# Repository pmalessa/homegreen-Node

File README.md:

# HomeGreen - self watering system
## Description
A self watering system for outdoor plants. This project contains the hardware and software files to completely build a HomeGreen node on your own.

The system is based on an inexpensive node, which is able to control up to 3 pumps and can be powered by nearly any conventional powerbank. It has a basic user interface using a 6-Digit 7-Segment Display combined with 4 touch buttons. As a pump, you could either use a 4-6V DC pump or a 5V relay to control a higher voltage pump. The node is designed to be water resistant and can be easily mounted using embedded magnets or a 3D printed holder.

## Repository structure
This repo contains everything you need to build a homegreen node on your own:

- hardware: The EAGLE PCB and GERBER files, BOM and models and dimensions for the case
- firmware: The firmware for the microcontroller (attiny88) on the node

## Hardware
The HomeGreen node PCB is designed to be enclosed in a 25mm diameter transparent pipe to be water resistant. The touch buttons can be used through the pipe without the need to open the case. The 2 ends need plastic caps, which could be easily 3D printed. one needs to be fully closed, while the other one needs to have an opening the for USB-A connector of the pump as well as the micro USB connector of the powerbank.

## Firmware
The firmware is written in low-level C++ and uses the PlatformIO framework. It is designed to run as energy efficient as possible to be able to run on a powerbank for a long time.

## Detailed description
The HomeGreen node contains the following main components:
- an attiny88 microcontroller as main controller
- a sophisticated power management circuit to be able to sleep and wake up the connected powerbank regularly
- a 6-Digit 7-Segment Display with its controller as user interface
- a 4-Channel touch button controller as user interface
- an I2C temperature sensor to measure the temperature of the environment
- a current limiter, step-up converter and a current measurement circuit to adjust and monitor the output power for the pump
- the ability to control up to 3 pumps sequentially using an additional HomeGreen Pump Hub

### Power management
The main issue of supplying your gadgets using a powerbank is the fact, that nearly all powerbanks shut off after a certain time of inactivity. As the sleep current draw of the HomeGreen node is substantially lower than any charge current the powerbank is designed for, it treats it as inactive and shuts off eventually. 

This led to the necessity to have a supercapacitor as an additional short-time energy storage onboard to be able to power the controller while in sleep and only wake the powerbank once the supercap is drained or it is time to enable the pump.

Additionally, each powerbank is behaving differently when it comes to the sleep and wake behavior. Some powerbanks wake up immediately once you connect the capacitive load of the supercap, while others require an additional substantial resistive load to enable its regulators. Strangely, some powerbanks even change their polarity and apply -2.5V to their output!

To support most of the available powerbanks on the market 2 MOSFETS back to back, combined with a charge pump and an additional controllable resistive load was necessary. Even with that, some powerbanks do not work reliably and should be avoided. A list of tested powerbanks will be added.

### User Interface
The HomeGreen Node consists of a 6-Digit 7-Segment display as well as 4 touch buttons to view its status and adjust all parameters to your needs. The HomeGreen Node can be used to control up to 3 pumps using an additional HomeGreen Pump Hub. Once connected, the user interface switches to the ability to adjust timing of each pump separately. However, if no Pump Hub is connected, it is simplyfied to control just one pump.

#### Sleep State
In its default sleep state, the 7-Segment Display is turned off and only the 2 Status LEDs are displaying its state. 
- If it blinks green once every 8 seconds, everything is fine. 
- If it blinks green twice and in a faster interval, it charges its supercap. This happens every 5-15mins. 
- If it blinks red, an error occured and the Node should be checked by waking it to get more details.
- If it is time to water the plants, it will wake itself and continue with the Pump State.
- To wake the Node, just touch one of its touch buttons. It will then try to wake the powerbank and will turn on its Display, once successful. It may take multiple tries sometimes depending on the model of powerbank. It then moves into Info State. If an error occured, it will switch into Error State after wake up before going to Info State.

#### Info State
In the info state, you see the set interval and duration of the pump cycle as well as the time left till the next pump cycle at one glance. If a Pump Hub is connected, you can switch between the config for each pump with a short press of the SET button.
- If no button is pressed, it shuts off and switches back to Sleep State after some time.
- To adjust the interval or duration of the pump cycle, long press the SET button and wait for the display to fade out and in. It now switched into Config State.
- To start a manual pump cycle, just long press the MANUAL button. It then switches into Pump State.

#### Config State
In the Config State, you can adjust the interval and duration of the pump cycle. The currently selected parameter is displayed by blinking its number.
- To increase the parameter, short press or hold the + button.
- To decrease the parameter, short press of hold the - button.
- To switch the selected parameter, short press the SET button.
- To save the newly configured parameters, long press the SET button. It switches to Info State then.
- If no button have been pressed for a longer period, changes are discarded and it switches to Info State.
- To get more advanced information and configuration options, long press the MANUAL button to switch to Advanced State.

#### Pump State
Once the pump interval elapsed or a manual pump cycle has been started, the Node switches into Pump State. In Pump State, an animation is displayed as well as the time left to pump in the current cycle. If a Pump Hub is connected, it will additionally display which pump is currently enabled.
- To increase the current pump cycle by 1 minute, short press the + button.
- To decrease the current pump cycle by 1 minute, short press the - button.
- To manually switch to the next pump, short press the SET button.
- To stop the current pump cycle, long press the MANUAL button.
- Once the pump duration of all pumps elapsed, the Node will switch to Info State to shortly display its current parameters, and after some time of inactivity it switches back to Sleep State.

#### Error State
If an error ocurred, the red led blinks to signal that something went wrong. To check for details, wake the node and it will switch to this state.
The following errors are possible:
- PB_ERR: Powerbank-Error - The node was not possible to wake the powerbank at its last wake up by a pump cycle or a user action. Check the charge state or cabling of the powerbank. Maybe that model is incompatible with the Node, check the list of tested powerbanks for hints.
- P1_ERR/P2_ERR/P3_ERR: Pump1/2/3-Error - There is an issue with the mentioned pump, the current draw had an anomaly. Maybe the cable is broken, the water tank is empty or the pump is clogged.
- EP_ERR: EEPROM-Error - There is an issue with the save state of the configuration. This rarely happens, but sometimes the config can get corrupted by battery drain. The config will be reset to default state and it has to be reconfigured.

The following interactions are possible:
- To clear the current error, short press any button.
- To ignore the current error permanently (until the next reset to defaults), long press the MANUAL button.

#### Advanced State
The Advanced State contains additional information and configuration options to move through.
The following informations are displayed:
- The build date of the firmware
- The build version of the firmware
- The current runtime in hours
- The total runtime in hours

The following interactions are possible:
- To move to the next information, short press the SET button
- To leave the Advanced State back to Info State, long press the SET button
- To reset all configurations to its default state, long press the MANUAL button. It then switches back to Info State.

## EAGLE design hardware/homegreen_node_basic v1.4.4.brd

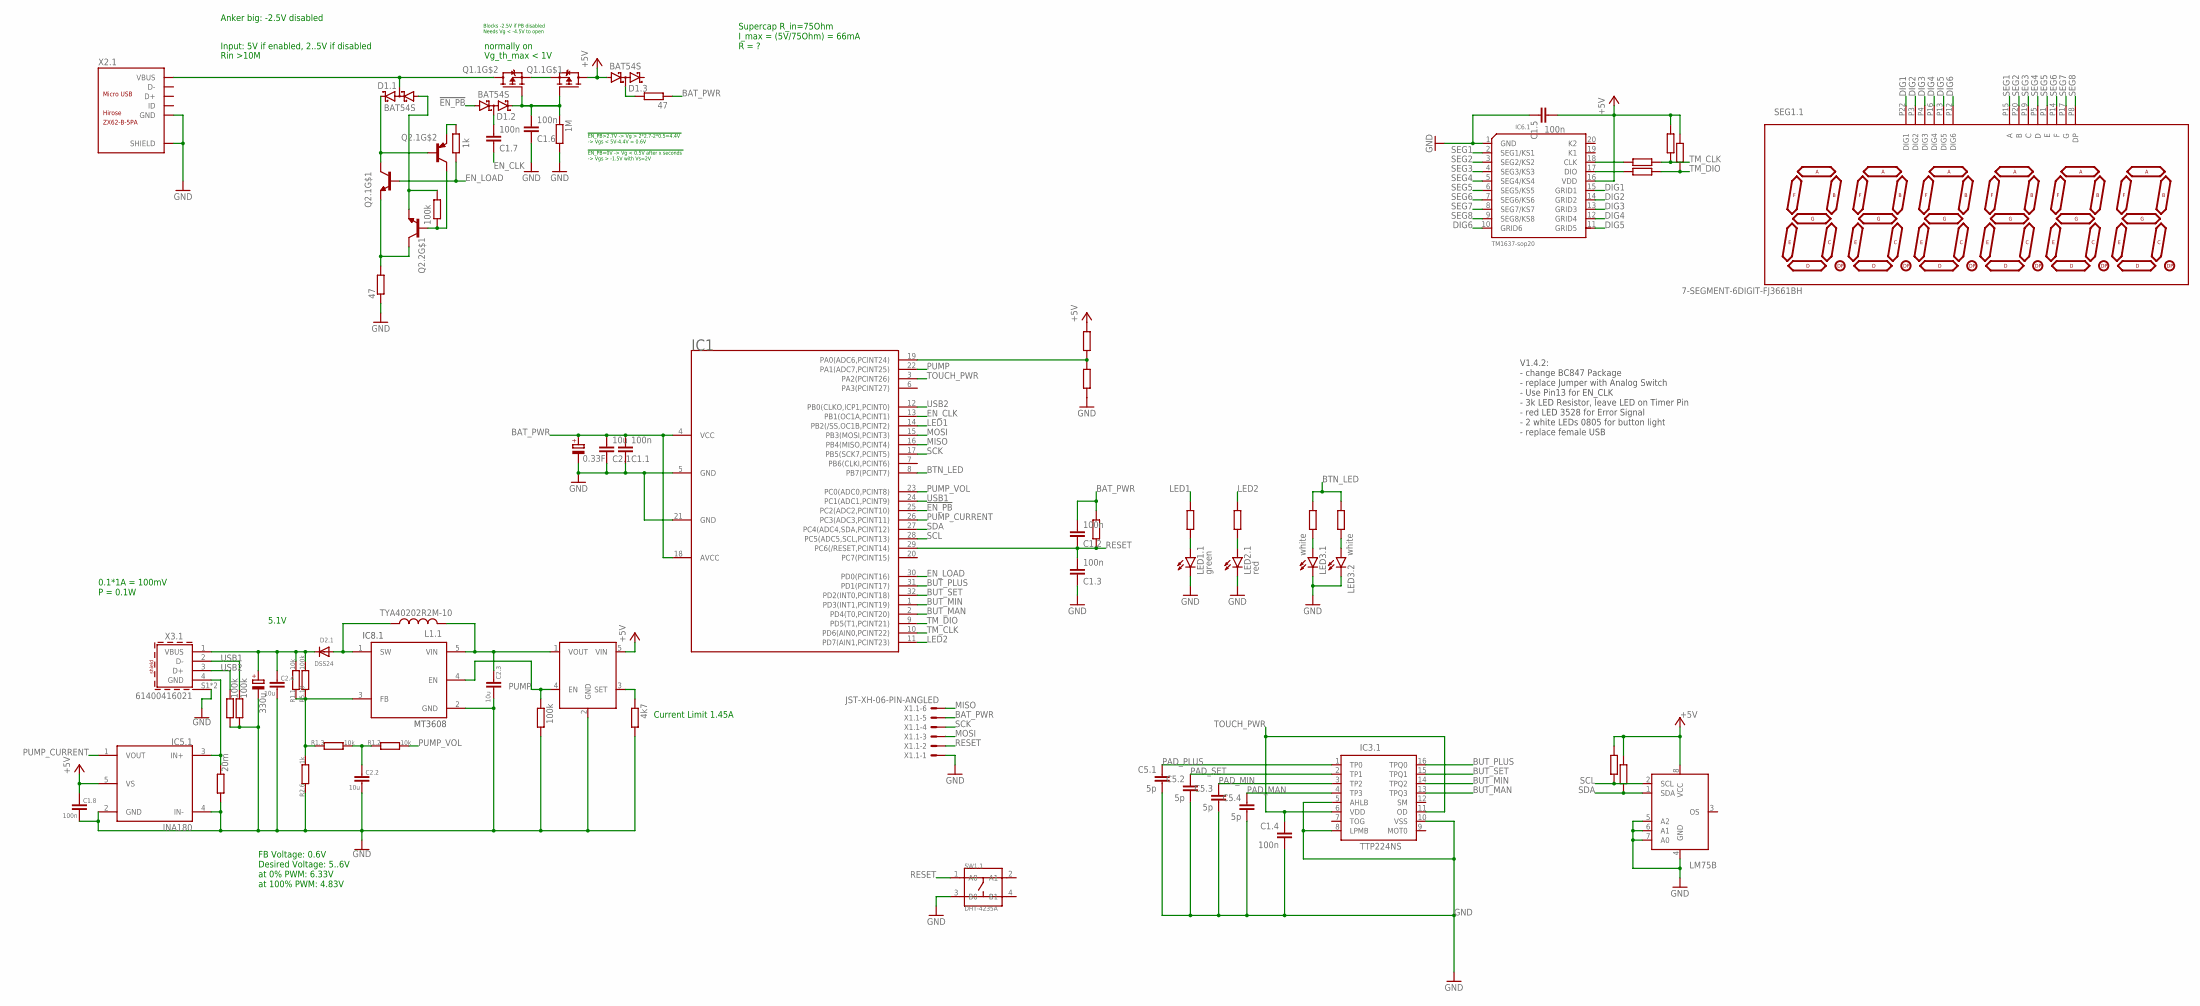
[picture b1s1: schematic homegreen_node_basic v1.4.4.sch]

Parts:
C1.1, C1.2, C1.3, C1.4, C1.5, C1.6, C1.7, C1.8: 100n; C0805
C2.1, C2.2, C2.3, C2.4: 10u; C0805
C3.1: 0.33F; C_FYD0H104ZF
C4.1: 330u; PANASONIC_D
C5.1, C5.2, C5.3, C5.4: 5p; C0805
D1.1, D1.2, D1.3: BAT54S; SOT23
D2.1: DSS24; SOD-123
IC1: ATTINY88; TQFP32-08
IC2.1: LM75B; SO8
IC3.1: TTP224NS; SSOP16
IC4.1: MT9700MT9700; SOT23-5
IC5.1: INA180; SOT23-5
IC6.1: TM1637-sop20; SOP20-1.27-12.7X7.65MM
IC8.1: MT3608; SOT23-6
L1.1: TYA40202R2M-10; WE-LQSH_4020
LED1.1: green; KA-3528ASYC
LED2.1: red; KA-3528ASYC
LED3.1, LED3.2: white; CHIPLED_0805
Q1.1: WST2011; SOT23-6
Q2.1, Q2.2: BC817DPN; SOT23-6
R1.1, R1.2, R1.3: 10k; R0805
R2.1, R2.2, R2.3, R2.4, R2.5, R2.6: 1k; R0805
R3.1, R3.2: 47; R0805
R4.1, R4.2: 3k; R0805
R5.1, R5.2, R5.3, R5.4, R5.5, R5.6, R5.7, R5.8, R5.9, R5.10: 100k; R0805
R6.1: 1M; R0805
R7.1, R7.2, R7.3: 4k7; R0805
R8.1: 20m; R0805
SEG1.1: 7-SEGMENT-6DIGIT-FJ3661BH; 7SEG_6D_FJ3661BH
SW1.1: DHT-4235A; SW4-SMD-4.2X3.2X2.5MM
X1.1: JST-XH-06-PIN-ANGLED; JST-XH-06-PACKAGE-ROUND-PAD-ANGLED
X2.1: ZX62-B-5PA
X3.1: 61400416021

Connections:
!EN_PB: D1.2.1 (A1), IC1.25 (PC2(ADC2,PCINT10))
+5V: C1.5.2, C1.8.1, D1.3.1 (A1), IC2.1.8 (VCC), IC4.1.5 (VIN), IC5.1.5 (VS), IC6.1.16 (VDD), Q1.1.6 (D), R5.3.1, R5.5.2, R5.6.2, R7.2.2, R7.3.2
BAT_PWR: C1.1.2, C1.2.2, C2.1.2, C3.1.+, IC1.4 (VCC), IC1.18 (AVCC), R3.2.1, R5.7.1, X1.1.5
BTN_LED: IC1.8 (PB7(PCINT7)), R2.1.2, R2.5.2
BUT_MAN: IC1.2 (PD4(T0,PCINT20)), IC3.1.13 (TPQ3)
BUT_MIN: IC1.1 (PD3(INT1,PCINT19)), IC3.1.14 (TPQ2)
BUT_PLUS: IC1.31 (PD1(PCINT17)), IC3.1.16 (TPQ0)
BUT_SET: IC1.32 (PD2(INT0,PCINT18)), IC3.1.15 (TPQ1)
DIG1: IC6.1.15 (GRID1), SEG1.1.P22 (DIG1)
DIG2: IC6.1.14 (GRID2), SEG1.1.P3 (DIG2)
DIG3: IC6.1.13 (GRID3), SEG1.1.P4 (DIG3)
DIG4: IC6.1.12 (GRID4), SEG1.1.P16 (DIG4)
DIG5: IC6.1.11 (GRID5), SEG1.1.P13 (DIG5)
DIG6: IC6.1.10 (GRID6), SEG1.1.P12 (DIG6)
EN_CLK: C1.7.1, IC1.13 (PB1(OC1A,PCINT1))
EN_LOAD: IC1.30 (PD0(PCINT16)), Q2.1.2 (B), R2.4.1
GND: C1.1.1, C1.3.1, C1.4.2, C1.5.1, C1.6.1, C1.8.2, C2.1.1, C2.2.2, C2.3.2, C2.4.2, C3.1.-, C4.1.-, C5.1.2, C5.2.2, C5.3.2, C5.4.2, IC1.5 (GND), IC1.21 (GND), IC2.1.4 (GND), IC2.1.5 (A2), IC2.1.6 (A1), IC2.1.7 (A0), IC3.1.5 (AHLB), IC3.1.8 (LPMB), IC3.1.10 (VSS), IC4.1.2 (GND), IC5.1.2 (GND), IC5.1.4 (IN-), IC6.1.1 (GND), IC8.1.2 (GND), LED1.1.C, LED2.1.C, LED3.1.C, LED3.2.C, R2.6.1, R3.1.1, R5.2.2, R5.4.2, R5.8.2, R5.9.2, R6.1.2, R7.1.2, R8.1.2, SW1.1.3 (B0), X1.1.1, X2.1.5 (GND), X2.1.P1 (SHIELD), X2.1.P2 (SHIELD), X2.1.P3 (SHIELD), X2.1.P4 (SHIELD), X2.1.P5 (SHIELD), X2.1.P6 (SHIELD), X3.1.S1 (SHIELD), X3.1.S2 (SHIELD)
LED1: IC1.14 (PB2(/SS,OC1B,PCINT2)), R4.1.2
LED2: IC1.11 (PD7(AIN1,PCINT23)), R4.2.2
MISO: IC1.16 (PB4(MISO,PCINT4)), X1.1.6
MOSI: IC1.15 (PB3(MOSI,PCINT3)), X1.1.3
unnamed: IC6.1.18 (CLK), R2.2.2
unnamed: C2.3.1, IC4.1.1 (VOUT), IC8.1.5 (VIN), L1.1.1
unnamed: Q1.1.2 (S), Q1.1.5 (S)
unnamed: IC6.1.17 (DIO), R2.3.2
unnamed: D1.3.3 (C1A2), R3.2.2
unnamed: Q2.1.1 (E), Q2.2.6 (C), R3.1.2
unnamed: LED1.1.A, R4.1.1
unnamed: IC1.19 (PA0(ADC6,PCINT24)), R5.3.2, R5.4.1
unnamed: C1.7.2, D1.2.3 (C1A2)
unnamed: Q2.1.4 (E), R2.4.2
unnamed: LED2.1.A, R4.2.1
unnamed: D1.1.2 (C2), Q2.1.5 (B), Q2.1.6 (C)
unnamed: C2.2.1, R1.2.1, R1.3.2
unnamed: D1.1.1 (A1), Q2.2.1 (E), R5.1.1
unnamed: Q2.1.3 (C), Q2.2.2 (B), R5.1.2
unnamed: LED3.1.A, R2.1.1
unnamed: C1.6.2, D1.2.2 (C2), Q1.1.1 (G), Q1.1.3 (G), R6.1.1
unnamed: LED3.2.A, R2.5.1
unnamed: C2.4.1, C4.1.+, D2.1.C, R1.1.2, R5.10.2, X3.1.1 (VBUS)
unnamed: IC5.1.3 (IN+), R8.1.1, X3.1.4 (GND)
unnamed: IC4.1.3 (SET), R7.1.1
unnamed: D2.1.A, IC8.1.1 (SW), L1.1.2
unnamed: IC8.1.3 (FB), R1.1.1, R1.3.1, R2.6.2, R5.10.1
PAD_MAN: C5.4.1, IC3.1.4 (TP3)
PAD_MIN: C5.3.1, IC3.1.3 (TP2)
PAD_PLUS: C5.1.1, IC3.1.1 (TP0)
PAD_SET: C5.2.1, IC3.1.2 (TP1)
PUMP: IC1.22 (PA1(ADC7,PCINT25)), IC4.1.4 (EN), IC8.1.4 (EN), R5.2.1
PUMP_CURRENT: IC1.26 (PC3(ADC3,PCINT11)), IC5.1.1 (VOUT)
PUMP_VOL: IC1.23 (PC0(ADC0,PCINT8)), R1.2.2
RESET: C1.2.1, C1.3.2, IC1.29 (PC6(/RESET,PCINT14)), R5.7.2, SW1.1.1 (A0), X1.1.2
SCK: IC1.17 (PB5(SCK7,PCINT5)), X1.1.4
SCL: IC1.28 (PC5(ADC5,SCL,PCINT13)), IC2.1.2 (SCL), R7.3.1
SDA: IC1.27 (PC4(ADC4,SDA,PCINT12)), IC2.1.1 (SDA), R7.2.1
SEG1: IC6.1.2 (SEG1/KS1), SEG1.1.P15 (A)
SEG2: IC6.1.3 (SEG2/KS2), SEG1.1.P20 (B)
SEG3: IC6.1.4 (SEG3/KS3), SEG1.1.P19 (C)
SEG4: IC6.1.5 (SEG4/KS4), SEG1.1.P5 (D)
SEG5: IC6.1.6 (SEG5/KS5), SEG1.1.P1 (E)
SEG6: IC6.1.7 (SEG6/KS6), SEG1.1.P14 (F)
SEG7: IC6.1.8 (SEG7/KS7), SEG1.1.P17 (G)
SEG8: IC6.1.9 (SEG8/KS8), SEG1.1.P8 (DP)
TM_CLK: IC1.10 (PD6(AIN0,PCINT22)), R2.2.1, R5.5.1
TM_DIO: IC1.9 (PD5(T1,PCINT21)), R2.3.1, R5.6.1
TOUCH_PWR: C1.4.1, IC1.3 (PA2(PCINT26)), IC3.1.6 (VDD), IC3.1.11 (OD)
USB1: IC1.24 (PC1(ADC1,PCINT9)), R5.9.1, X3.1.2 (D-)
USB2: IC1.12 (PB0(CLKO,ICP1,PCINT0)), R5.8.1, X3.1.3 (D+)
VBUS: D1.1.3 (C1A2), Q1.1.4 (D), X2.1.1 (VBUS)

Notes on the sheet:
V1.4.2: - change BC847 Package - replace Jumper with Analog Switch - Use Pin13 for EN_CLK - 3k LED Resistor, leave LED on Timer Pin - red LED 3528 for Error Signal - 2 white LEDs 0805 for button light - replace female USB
normally on
Input: 5V if enabled, 2..5V if disabled
Vg_th_max < 1V
Supercap R_in=75Ohm I_max = (5V/75Ohm) = 66mA R = ?
Rin >10M
!EN_PB>2.7V -> Vg > 2*2.7-2*0.5=4.4V -> Vgs < 5V-4.4V = 0.6V !EN_PB=0V -> Vg < 0.5V after x seconds -> Vgs > -1.5V with Vs=2V
Anker big: -2.5V disabled
Blocks -2.5V if PB disabled Needs Vg < -4.5V to open
5.1V
Current Limit 1.45A
FB Voltage: 0.6V Desired Voltage: 5..6V at 0% PWM: 6.33V at 100% PWM: 4.83V
0.1*1A = 100mV P = 0.1W

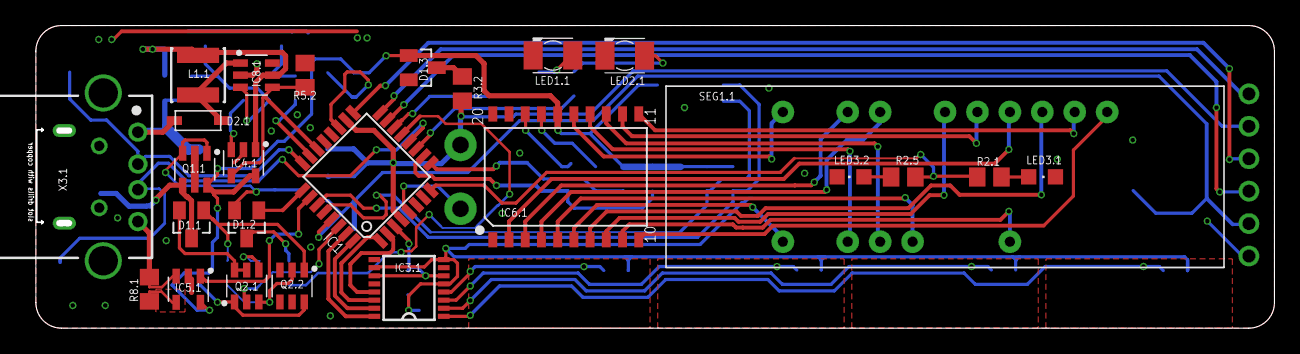
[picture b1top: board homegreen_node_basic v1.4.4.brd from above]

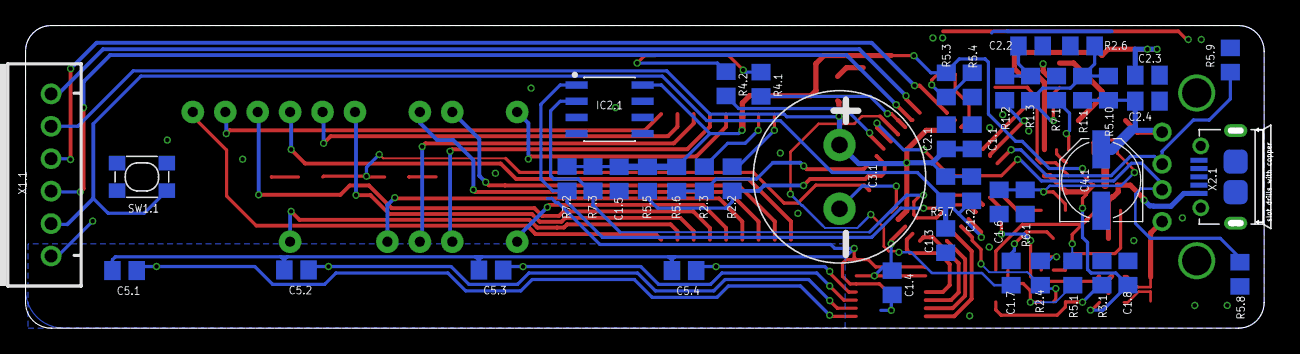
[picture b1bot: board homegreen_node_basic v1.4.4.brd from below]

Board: 2 copper layers, 97.3 x 23.2 mm, 70 parts (45 on the bottom side), 69 nets.

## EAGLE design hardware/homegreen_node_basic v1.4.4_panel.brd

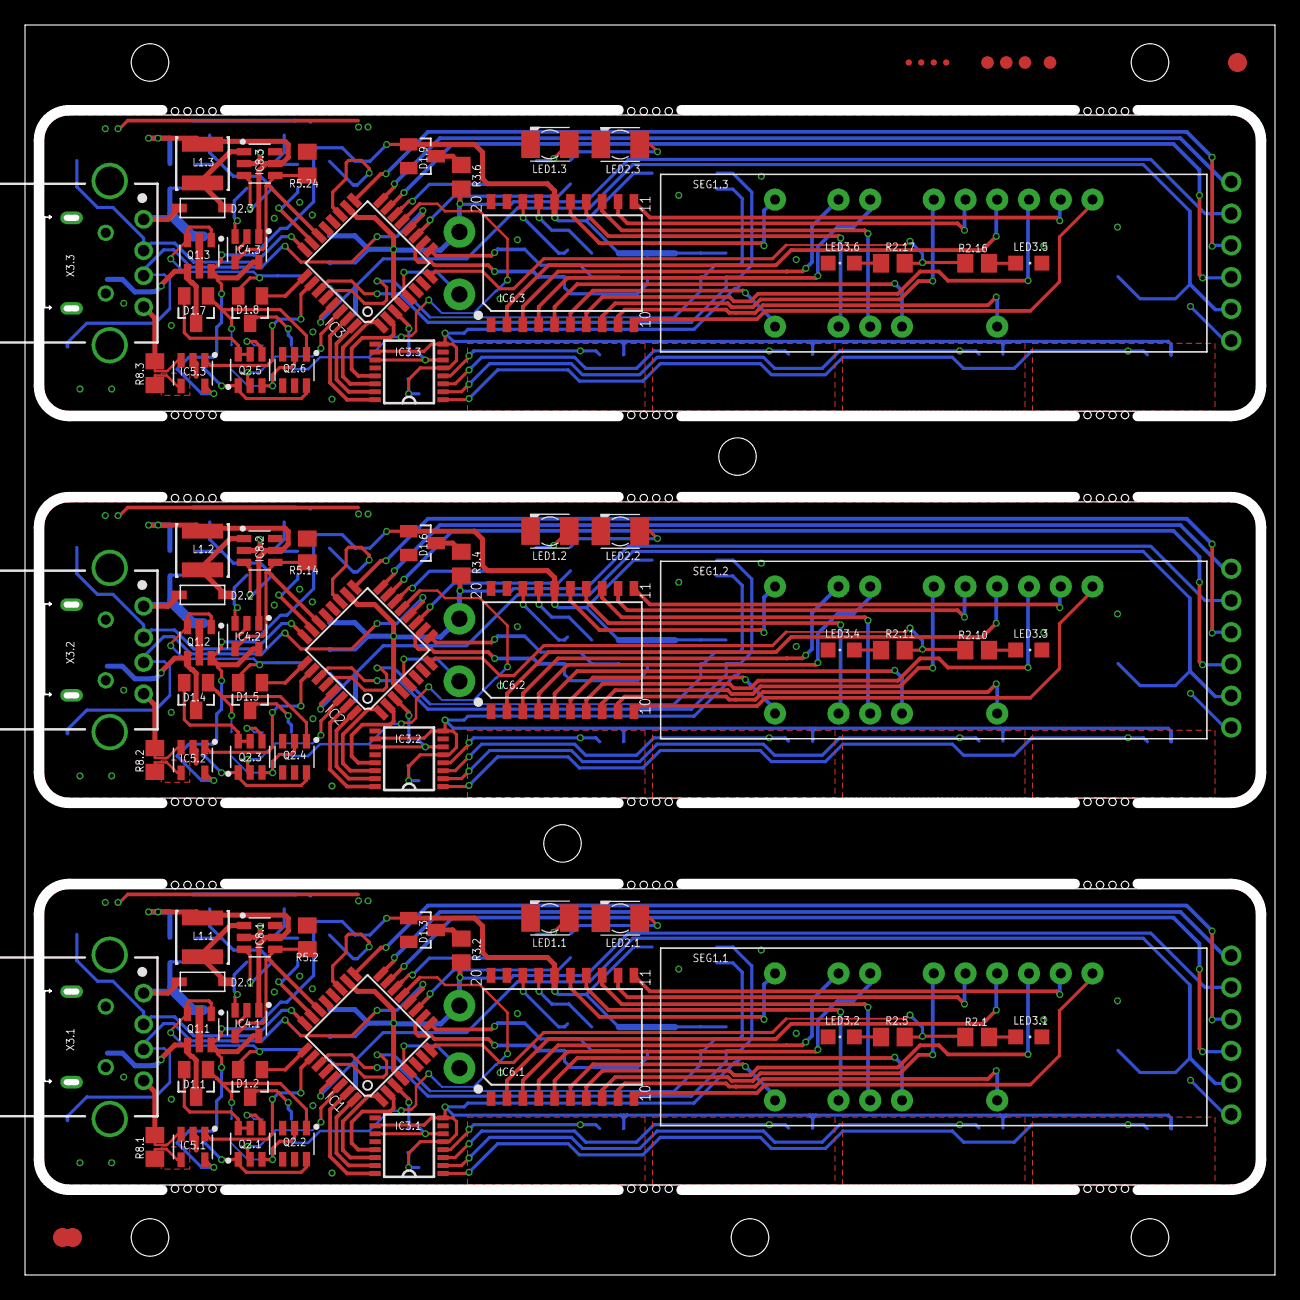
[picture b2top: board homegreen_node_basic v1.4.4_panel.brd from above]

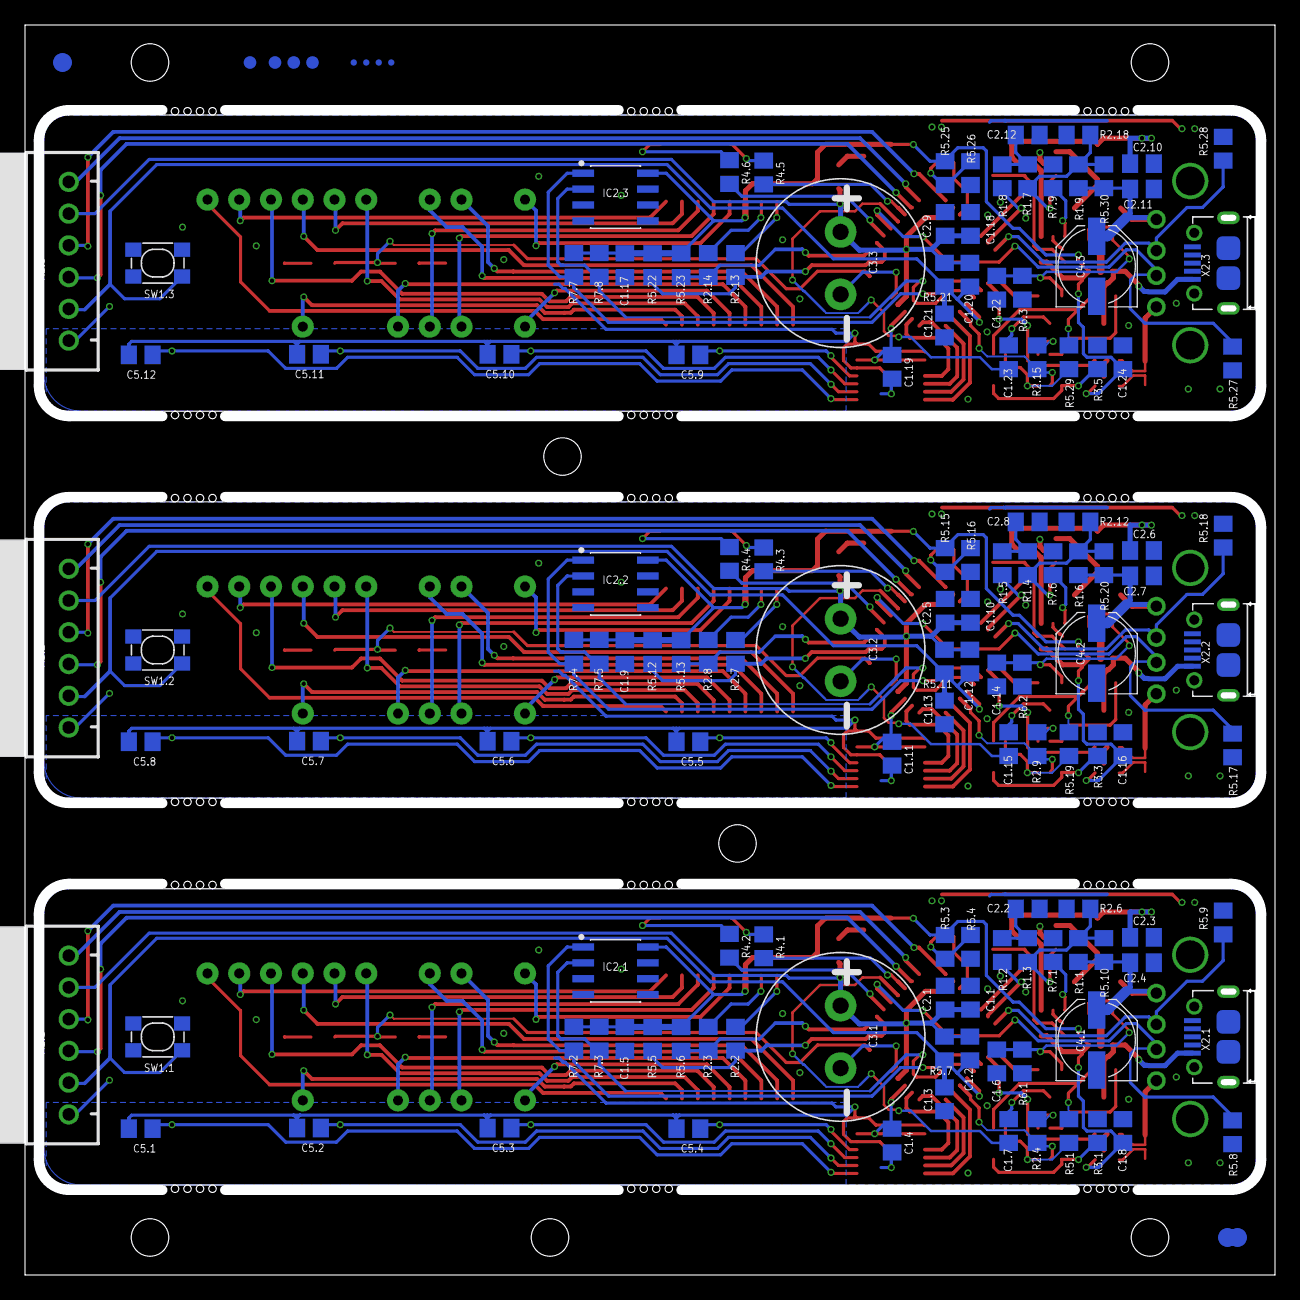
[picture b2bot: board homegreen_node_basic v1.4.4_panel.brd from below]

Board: 2 copper layers, 99.2 x 99.2 mm, 221 parts (135 on the bottom side), 207 nets.

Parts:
C1.1, C1.2, C1.3, C1.4, C1.5, C1.6, C1.7, C1.8, C1.9, C1.10, C1.11, C1.12, C1.13, C1.14, C1.15, C1.16, C1.17, C1.18, C1.19, C1.20, C1.21, C1.22, C1.23, C1.24: 100n; C0805
C2.1, C2.2, C2.3, C2.4, C2.5, C2.6, C2.7, C2.8, C2.9, C2.10, C2.11, C2.12: 10u; C0805
C3.1, C3.2, C3.3: 0.33F; C_FYD0H104ZF
C4.1, C4.2, C4.3: 330u; PANASONIC_D
C5.1, C5.2, C5.3, C5.4, C5.5, C5.6, C5.7, C5.8, C5.9, C5.10, C5.11, C5.12: 5p; C0805
D1.1, D1.2, D1.3, D1.4, D1.5, D1.6, D1.7, D1.8, D1.9: BAT54S; SOT23
D2.1, D2.2, D2.3: DSS24; SOD-123
E$1, E$2, E$3: FID_060_P
E$4, E$5, E$6, E$7: FID_040_P
E$8, E$9, E$10, E$11: FID_020_P
IC1, IC2, IC3: TQFP32-08
IC2.1, IC2.2, IC2.3: LM75B; SO8
IC3.1, IC3.2, IC3.3: TTP224NS; SSOP16
IC4.1, IC4.2, IC4.3: MT9700MT9700; SOT23-5
IC5.1, IC5.2, IC5.3: INA180; SOT23-5
IC6.1, IC6.2, IC6.3: TM1637-sop20; SOP20-1.27-12.7X7.65MM
IC8.1, IC8.2, IC8.3: MT3608; SOT23-6
L1.1, L1.2, L1.3: TYA40202R2M-10; WE-LQSH_4020
LED1.1, LED1.2, LED1.3: green; KA-3528ASYC
LED2.1, LED2.2, LED2.3: red; KA-3528ASYC
LED3.1, LED3.2, LED3.3, LED3.4, LED3.5, LED3.6: white; CHIPLED_0805
Q1.1, Q1.2, Q1.3: WST2011; SOT23-6
Q2.1, Q2.2, Q2.3, Q2.4, Q2.5, Q2.6: BC817DPN; SOT23-6
R1.1, R1.2, R1.3, R1.4, R1.5, R1.6, R1.7, R1.8, R1.9: 10k; R0805
R2.1, R2.2, R2.3, R2.4, R2.5, R2.6, R2.7, R2.8, R2.9, R2.10, R2.11, R2.12, R2.13, R2.14, R2.15, R2.16, R2.17, R2.18: 1k; R0805
R3.1, R3.2, R3.3, R3.4, R3.5, R3.6: 47; R0805
R4.1, R4.2, R4.3, R4.4, R4.5, R4.6: 3k; R0805
R5.1, R5.2, R5.3, R5.4, R5.5, R5.6, R5.7, R5.8, R5.9, R5.10, R5.11, R5.12, R5.13, R5.14, R5.15, R5.16, R5.17, R5.18, R5.19, R5.20, R5.21, R5.22, R5.23, R5.24, R5.25, R5.26, R5.27, R5.28, R5.29, R5.30: 100k; R0805
R6.1, R6.2, R6.3: 1M; R0805
R7.1, R7.2, R7.3, R7.4, R7.5, R7.6, R7.7, R7.8, R7.9: 4k7; R0805
R8.1, R8.2, R8.3: 20m; R0805
SEG1.1, SEG1.2, SEG1.3: 7-SEGMENT-6DIGIT-FJ3661BH; 7SEG_6D_FJ3661BH
SW1.1, SW1.2, SW1.3: DHT-4235A; SW4-SMD-4.2X3.2X2.5MM
X1.1, X1.2, X1.3: JST-XH-06-PIN-ANGLED; JST-XH-06-PACKAGE-ROUND-PAD-ANGLED
X2.1, X2.2, X2.3: ZX62-B-5PA
X3.1, X3.2, X3.3: 61400416021

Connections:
!EN_PB: D1.2.1, IC1.25
!EN_PB1: D1.5.1, IC2.25
!EN_PB2: D1.8.1, IC3.25
+5V: C1.5.2, C1.8.1, D1.3.1, IC2.1.8, IC4.1.5, IC5.1.5, IC6.1.16, Q1.1.6, R5.3.1, R5.5.2, R5.6.2, R7.2.2, R7.3.2
+5V1: C1.9.2, C1.16.1, D1.6.1, IC2.2.8, IC4.2.5, IC5.2.5, IC6.2.16, Q1.2.6, R5.12.2, R5.13.2, R5.15.1, R7.4.2, R7.5.2
+5V2: C1.17.2, C1.24.1, D1.9.1, IC2.3.8, IC4.3.5, IC5.3.5, IC6.3.16, Q1.3.6, R5.22.2, R5.23.2, R5.25.1, R7.7.2, R7.8.2
BAT_PWR: C1.1.2, C1.2.2, C2.1.2, C3.1.+, IC1.4, IC1.18, R3.2.1, R5.7.1, X1.1.5
BAT_PWR1: C1.10.2, C1.12.2, C2.5.2, C3.2.+, IC2.4, IC2.18, R3.4.1, R5.11.1, X1.2.5
BAT_PWR2: C1.18.2, C1.20.2, C2.9.2, C3.3.+, IC3.4, IC3.18, R3.6.1, R5.21.1, X1.3.5
BTN_LED: IC1.8, R2.1.2, R2.5.2
BTN_LED1: IC2.8, R2.10.2, R2.11.2
BTN_LED2: IC3.8, R2.16.2, R2.17.2
BUT_MAN: IC1.2, IC3.1.13
BUT_MAN1: IC2.2, IC3.2.13
BUT_MAN2: IC3.2, IC3.3.13
BUT_MIN: IC1.1, IC3.1.14
BUT_MIN1: IC2.1, IC3.2.14
BUT_MIN2: IC3.1, IC3.3.14
BUT_PLUS: IC1.31, IC3.1.16
BUT_PLUS1: IC2.31, IC3.2.16
BUT_PLUS2: IC3.31, IC3.3.16
BUT_SET: IC1.32, IC3.1.15
BUT_SET1: IC2.32, IC3.2.15
BUT_SET2: IC3.32, IC3.3.15
DIG1: IC6.1.15, SEG1.1.P22
DIG2: IC6.1.14, SEG1.1.P3
DIG3: IC6.1.13, SEG1.1.P4
DIG4: IC6.1.12, SEG1.1.P16
DIG5: IC6.1.11, SEG1.1.P13
DIG6: IC6.1.10, SEG1.1.P12
DIG7: IC6.2.10, SEG1.2.P12
DIG8: IC6.2.11, SEG1.2.P13
DIG9: IC6.2.12, SEG1.2.P16
DIG10: IC6.2.13, SEG1.2.P4
DIG11: IC6.2.14, SEG1.2.P3
DIG12: IC6.2.15, SEG1.2.P22
DIG13: IC6.3.10, SEG1.3.P12
DIG14: IC6.3.11, SEG1.3.P13
DIG15: IC6.3.12, SEG1.3.P16
DIG16: IC6.3.13, SEG1.3.P4
DIG17: IC6.3.14, SEG1.3.P3
DIG18: IC6.3.15, SEG1.3.P22
EN_CLK: C1.7.1, IC1.13
EN_CLK1: C1.15.1, IC2.13
EN_CLK2: C1.23.1, IC3.13
EN_LOAD: IC1.30, Q2.1.2, R2.4.1
EN_LOAD1: IC2.30, Q2.3.2, R2.9.1
EN_LOAD2: IC3.30, Q2.5.2, R2.15.1
GND: C1.1.1, C1.3.1, C1.4.2, C1.5.1, C1.6.1, C1.8.2, C2.1.1, C2.2.2, C2.3.2, C2.4.2, C3.1.-, C4.1.-, C5.1.2, C5.2.2, C5.3.2, C5.4.2, IC1.5, IC1.21, IC2.1.4, IC2.1.5, IC2.1.6, IC2.1.7, IC3.1.5, IC3.1.8, IC3.1.10, IC4.1.2, IC5.1.2, IC5.1.4, IC6.1.1, IC8.1.2, LED1.1.C, LED2.1.C, LED3.1.C, LED3.2.C, R2.6.1, R3.1.1, R5.2.2, R5.4.2, R5.8.2, R5.9.2, R6.1.2, R7.1.2, R8.1.2, SW1.1.3, X1.1.1, X2.1.5, X2.1.P1, X2.1.P2, X2.1.P3, X2.1.P4, X2.1.P5, X2.1.P6, X3.1.S1, X3.1.S2
GND1: C1.9.1, C1.10.1, C1.11.2, C1.13.1, C1.14.1, C1.16.2, C2.5.1, C2.6.2, C2.7.2, C2.8.2, C3.2.-, C4.2.-, C5.5.2, C5.6.2, C5.7.2, C5.8.2, IC2.5, IC2.21, IC2.2.4, IC2.2.5, IC2.2.6, IC2.2.7, IC3.2.5, IC3.2.8, IC3.2.10, IC4.2.2, IC5.2.2, IC5.2.4, IC6.2.1, IC8.2.2, LED1.2.C, LED2.2.C, LED3.3.C, LED3.4.C, R2.12.1, R3.3.1, R5.14.2, R5.16.2, R5.17.2, R5.18.2, R6.2.2, R7.6.2, R8.2.2, SW1.2.3, X1.2.1, X2.2.5, X2.2.P1, X2.2.P2, X2.2.P3, X2.2.P4, X2.2.P5, X2.2.P6, X3.2.S1, X3.2.S2
GND4: C1.17.1, C1.18.1, C1.19.2, C1.21.1, C1.22.1, C1.24.2, C2.9.1, C2.10.2, C2.11.2, C2.12.2, C3.3.-, C4.3.-, C5.9.2, C5.10.2, C5.11.2, C5.12.2, IC2.3.4, IC2.3.5, IC2.3.6, IC2.3.7, IC3.5, IC3.21, IC3.3.5, IC3.3.8, IC3.3.10, IC4.3.2, IC5.3.2, IC5.3.4, IC6.3.1, IC8.3.2, LED1.3.C, LED2.3.C, LED3.5.C, LED3.6.C, R2.18.1, R3.5.1, R5.24.2, R5.26.2, R5.27.2, R5.28.2, R6.3.2, R7.9.2, R8.3.2, SW1.3.3, X1.3.1, X2.3.5, X2.3.P1, X2.3.P2, X2.3.P3, X2.3.P4, X2.3.P5, X2.3.P6, X3.3.S1, X3.3.S2
LED1: IC1.14, R4.1.2
LED2: IC1.11, R4.2.2
LED3: IC2.11, R4.4.2
LED4: IC2.14, R4.3.2
LED5: IC3.11, R4.6.2
LED6: IC3.14, R4.5.2
MISO: IC1.16, X1.1.6
MISO1: IC2.16, X1.2.6
MISO2: IC3.16, X1.3.6
MOSI: IC1.15, X1.1.3
MOSI1: IC2.15, X1.2.3
MOSI2: IC3.15, X1.3.3
unnamed: IC6.1.18, R2.2.2
unnamed: C2.3.1, IC4.1.1, IC8.1.5, L1.1.1
unnamed: Q1.1.2, Q1.1.5
unnamed: IC6.1.17, R2.3.2
unnamed: D1.3.3, R3.2.2
unnamed: Q2.1.1, Q2.2.6, R3.1.2
unnamed: LED1.1.A, R4.1.1
unnamed: IC1.19, R5.3.2, R5.4.1
unnamed: C1.7.2, D1.2.3
unnamed: Q2.1.4, R2.4.2
unnamed: LED2.1.A, R4.2.1
unnamed: D1.1.2, Q2.1.5, Q2.1.6
unnamed: C2.2.1, R1.2.1, R1.3.2
unnamed: D1.1.1, Q2.2.1, R5.1.1
unnamed: Q2.1.3, Q2.2.2, R5.1.2
unnamed: LED3.1.A, R2.1.1
unnamed: C1.6.2, D1.2.2, Q1.1.1, Q1.1.3, R6.1.1
unnamed: LED3.2.A, R2.5.1
unnamed: C2.4.1, C4.1.+, D2.1.C, R1.1.2, R5.10.2, X3.1.1
unnamed: D1.6.3, R3.4.2
unnamed: LED1.2.A, R4.3.1
unnamed: IC5.1.3, R8.1.1, X3.1.4
unnamed: IC4.1.3, R7.1.1
unnamed: IC6.2.18, R2.7.2
unnamed: IC6.2.17, R2.8.2
unnamed: IC2.19, R5.15.2, R5.16.1
unnamed: C1.14.2, D1.5.2, Q1.2.1, Q1.2.3, R6.2.1
unnamed: Q2.3.1, Q2.4.6, R3.3.2
unnamed: D1.4.2, Q2.3.5, Q2.3.6
unnamed: D2.1.A, IC8.1.1, L1.1.2
unnamed: IC8.1.3, R1.1.1, R1.3.1, R2.6.2, R5.10.1
unnamed: D1.4.1, Q2.4.1, R5.19.1
unnamed: Q2.3.3, Q2.4.2, R5.19.2
unnamed: Q2.3.4, R2.9.2
unnamed: Q1.2.2, Q1.2.5
unnamed: C1.15.2, D1.5.3
unnamed: LED2.2.A, R4.4.1
unnamed: LED3.3.A, R2.10.1
unnamed: LED3.4.A, R2.11.1
unnamed: D2.2.A, IC8.2.1, L1.2.2
unnamed: IC8.2.3, R1.4.1, R1.6.1, R2.12.2, R5.20.1
unnamed: C2.7.1, C4.2.+, D2.2.C, R1.6.2, R5.20.2, X3.2.1
unnamed: C2.8.1, R1.4.2, R1.5.1
unnamed: C2.6.1, IC4.2.1, IC8.2.5, L1.2.1
unnamed: IC4.2.3, R7.6.1
unnamed: IC5.2.3, R8.2.1, X3.2.4
unnamed: D1.9.3, R3.6.2
unnamed: LED1.3.A, R4.5.1
unnamed: IC6.3.18, R2.13.2
unnamed: IC6.3.17, R2.14.2
unnamed: IC3.19, R5.25.2, R5.26.1
unnamed: C1.22.2, D1.8.2, Q1.3.1, Q1.3.3, R6.3.1
unnamed: Q2.5.1, Q2.6.6, R3.5.2
unnamed: D1.7.2, Q2.5.5, Q2.5.6
unnamed: D1.7.1, Q2.6.1, R5.29.1
unnamed: Q2.5.3, Q2.6.2, R5.29.2
unnamed: Q2.5.4, R2.15.2
unnamed: Q1.3.2, Q1.3.5
unnamed: C1.23.2, D1.8.3
unnamed: LED2.3.A, R4.6.1
unnamed: LED3.5.A, R2.16.1
unnamed: LED3.6.A, R2.17.1
unnamed: D2.3.A, IC8.3.1, L1.3.2
unnamed: IC8.3.3, R1.7.1, R1.9.1, R2.18.2, R5.30.1
unnamed: C2.11.1, C4.3.+, D2.3.C, R1.9.2, R5.30.2, X3.3.1
unnamed: C2.12.1, R1.7.2, R1.8.1
unnamed: C2.10.1, IC4.3.1, IC8.3.5, L1.3.1
unnamed: IC4.3.3, R7.9.1
unnamed: IC5.3.3, R8.3.1, X3.3.4
PAD_MAN: C5.4.1, IC3.1.4
PAD_MAN1: C5.5.1, IC3.2.4
PAD_MAN2: C5.9.1, IC3.3.4
PAD_MIN: C5.3.1, IC3.1.3
PAD_MIN1: C5.6.1, IC3.2.3
PAD_MIN2: C5.10.1, IC3.3.3
PAD_PLUS: C5.1.1, IC3.1.1
PAD_PLUS1: C5.8.1, IC3.2.1
PAD_PLUS2: C5.12.1, IC3.3.1
PAD_SET: C5.2.1, IC3.1.2
PAD_SET1: C5.7.1, IC3.2.2
PAD_SET2: C5.11.1, IC3.3.2
PUMP: IC1.22, IC4.1.4, IC8.1.4, R5.2.1
PUMP1: IC2.22, IC4.2.4, IC8.2.4, R5.14.1
PUMP2: IC3.22, IC4.3.4, IC8.3.4, R5.24.1
PUMP_CURRENT: IC1.26, IC5.1.1
PUMP_CURRENT1: IC2.26, IC5.2.1
PUMP_CURRENT2: IC3.26, IC5.3.1
PUMP_VOL: IC1.23, R1.2.2
PUMP_VOL1: IC2.23, R1.5.2
PUMP_VOL2: IC3.23, R1.8.2
RESET: C1.2.1, C1.3.2, IC1.29, R5.7.2, SW1.1.1, X1.1.2
RESET1: C1.12.1, C1.13.2, IC2.29, R5.11.2, SW1.2.1, X1.2.2
RESET2: C1.20.1, C1.21.2, IC3.29, R5.21.2, SW1.3.1, X1.3.2
SCK: IC1.17, X1.1.4
SCK1: IC2.17, X1.2.4
SCK2: IC3.17, X1.3.4
SCL: IC1.28, IC2.1.2, R7.3.1
SCL1: IC2.28, IC2.2.2, R7.5.1
SCL2: IC2.3.2, IC3.28, R7.8.1
SDA: IC1.27, IC2.1.1, R7.2.1
SDA1: IC2.27, IC2.2.1, R7.4.1
SDA2: IC2.3.1, IC3.27, R7.7.1
SEG1: IC6.1.2, SEG1.1.P15
SEG2: IC6.1.3, SEG1.1.P20
SEG3: IC6.1.4, SEG1.1.P19
SEG4: IC6.1.5, SEG1.1.P5
SEG5: IC6.1.6, SEG1.1.P1
SEG6: IC6.1.7, SEG1.1.P14
SEG7: IC6.1.8, SEG1.1.P17
SEG8: IC6.1.9, SEG1.1.P8
SEG9: IC6.2.2, SEG1.2.P15
SEG10: IC6.2.3, SEG1.2.P20
SEG11: IC6.2.4, SEG1.2.P19
SEG12: IC6.2.5, SEG1.2.P5
SEG13: IC6.2.6, SEG1.2.P1
SEG14: IC6.2.7, SEG1.2.P14
SEG15: IC6.2.8, SEG1.2.P17
SEG16: IC6.2.9, SEG1.2.P8
SEG17: IC6.3.2, SEG1.3.P15
SEG18: IC6.3.3, SEG1.3.P20
SEG19: IC6.3.4, SEG1.3.P19
SEG20: IC6.3.5, SEG1.3.P5
SEG21: IC6.3.6, SEG1.3.P1
SEG22: IC6.3.7, SEG1.3.P14
SEG23: IC6.3.8, SEG1.3.P17
SEG24: IC6.3.9, SEG1.3.P8
TM_CLK: IC1.10, R2.2.1, R5.5.1
TM_CLK1: IC2.10, R2.7.1, R5.12.1
TM_CLK2: IC3.10, R2.13.1, R5.22.1
TM_DIO: IC1.9, R2.3.1, R5.6.1
TM_DIO1: IC2.9, R2.8.1, R5.13.1
TM_DIO2: IC3.9, R2.14.1, R5.23.1
TOUCH_PWR: C1.4.1, IC1.3, IC3.1.6, IC3.1.11
TOUCH_PWR1: C1.11.1, IC2.3, IC3.2.6, IC3.2.11
TOUCH_PWR2: C1.19.1, IC3.3, IC3.3.6, IC3.3.11
USB1: IC1.24, R5.9.1, X3.1.2
USB2: IC1.12, R5.8.1, X3.1.3
USB3: IC2.24, R5.18.1, X3.2.2
USB4: IC2.12, R5.17.1, X3.2.3
USB5: IC3.24, R5.28.1, X3.3.2
USB6: IC3.12, R5.27.1, X3.3.3
VBUS: D1.1.3, Q1.1.4, X2.1.1
VBUS1: D1.4.3, Q1.2.4, X2.2.1
VBUS2: D1.7.3, Q1.3.4, X2.3.1

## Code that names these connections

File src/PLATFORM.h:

/*
 * PLATFORM.h
 *
 *  Created on: 25.01.2019
 *      Author: pmale
 */

#ifndef PLATFORM_H_
#define PLATFORM_H_

#include <avr/io.h>
#include <util/delay.h>
#include <avr/interrupt.h>
#include <avr/pgmspace.h>
#include <avr/sleep.h>
#include <stdlib.h>

#define BUILD_DAY 05
#define BUILD_MONTH 07
#define BUILD_YEAR 22
#define BUILD_VERSION_MAJOR 1
#define BUILD_VERSION_MINOR 4
#define BUILD_VERSION_PATCH 7

#ifdef HG_BASIC_HW_1_4_4

#define FEATURE_PUMP_STRENGTH
#define FEATURE_PUMP_SENSOR

#define CHK_5V_DDR DDRA
#define CHK_5V_PORT PORTA
#define CHK_5V_PIN PA0
#define CHK_5V_PINREG PINA

#define PUMP_DDR DDRA
#define PUMP_PORT PORTA
#define PUMP_PIN PA1

#define TOUCH_PWR_DDR DDRA
#define TOUCH_PWR_PORT PORTA
#define TOUCH_PWR_PIN PA2

#define USB_OUT_P_DDR DDRB
#define USB_OUT_P_PORT PORTB
#define USB_OUT_P_PIN PB0
#define USB_OUT_P_PINREG PINB

#define EN_CLK_DDR DDRB
#define EN_CLK_PORT PORTB
#define EN_CLK_PIN PB1

#define LED_GREEN_DDR DDRB
#define LED_GREEN_PORT PORTB
#define LED_GREEN_PIN PB2

#define LED_BTN_DDR DDRB
#define LED_BTN_PORT PORTB
#define LED_BTN_PIN PB7

#define PUMP_VOL_DDR DDRC
#define PUMP_VOL_PORT PORTC
#define PUMP_VOL_PIN PC0

#define USB_OUT_M_DDR DDRC
#define USB_OUT_M_PORT PORTC
#define USB_OUT_M_PIN PC1
#define USB_OUT_M_PINREG PINC

#define EN_PB_DDR DDRC
#define EN_PB_PORT PORTC
#define EN_PB_PIN PC2

#define PUMP_CUR_DDR DDRC
#define PUMP_CUR_PORT PORTC
#define PUMP_CUR_PIN PC3
#define PUMP_CUR_PINREG PINC

#define I2C_SDA_DDR DDRC
#define I2C_SDA_PORT PORTC
#define I2C_SDA_PIN PC4

#define I2C_SCL_DDR DDRC
#define I2C_SCL_PORT PORTC
#define I2C_SCL_PIN PC5

#define EN_LOAD_DDR DDRD
#define EN_LOAD_PORT PORTD
#define EN_LOAD_PIN PD0

#define TM_OUT          PORTD
#define TM_IN           PIND
#define TM_DDR          DDRD
#define TM_BIT_DAT      _BV(PD5)
#define TM_BIT_CLK      _BV(PD6)

#define LED_RED_DDR DDRD
#define LED_RED_PORT PORTD
#define LED_RED_PIN PD7

#elif defined(HG_BASIC_HW_1_4_3)
#define DEBUG1_DDR DDRC
#define DEBUG1_PORT PORTC
#define DEBUG1_PIN PC0

#define EN_PB_DDR DDRC
#define EN_PB_PORT PORTC
#define EN_PB_PIN PC2

#define EN_LOAD_DDR DDRC
#define EN_LOAD_PORT PORTC
#define EN_LOAD_PIN PC3

#define CHK_5V_DDR DDRA
#define CHK_5V_PORT PORTA
#define CHK_5V_PIN PA0
#define CHK_5V_PINREG PINA

#define TOUCH_PWR_DDR DDRA
#define TOUCH_PWR_PORT PORTA
#define TOUCH_PWR_PIN PA2

#define I2C_SCL_DDR DDRC
#define I2C_SCL_PORT PORTC
#define I2C_SCL_PIN PC5

#define I2C_SDA_DDR DDRC
#define I2C_SDA_PORT PORTC
#define I2C_SDA_PIN PC4

#define EN_CLK_DDR DDRB
#define EN_CLK_PORT PORTB
#define EN_CLK_PIN PB1

#define LED_RED_DDR DDRD
#define LED_RED_PORT PORTD
#define LED_RED_PIN PD7

#define LED_GREEN_DDR DDRB
#define LED_GREEN_PORT PORTB
#define LED_GREEN_PIN PB2

#define LED_BTN_DDR DDRB
#define LED_BTN_PORT PORTB
#define LED_BTN_PIN PB7

#define PUMP_DDR DDRA
#define PUMP_PORT PORTA
#define PUMP_PIN PA1

#define USB_OUT_M_DDR DDRC
#define USB_OUT_M_PORT PORTC
#define USB_OUT_M_PIN PC1
#define USB_OUT_M_PINREG PINC

#define USB_OUT_P_DDR DDRB
#define USB_OUT_P_PORT PORTB
#define USB_OUT_P_PIN PB0
#define USB_OUT_P_PINREG PINB

#define USB_IN_SW_DDR DDRC
#define USB_IN_SW_PORT PORTC
#define USB_IN_SW_PIN PC7

#define TM_OUT          PORTD
#define TM_IN           PIND
#define TM_DDR          DDRD
#define TM_BIT_CLK      _BV(PD6)
#define TM_BIT_DAT      _BV(PD5)
#endif

//#define SLEEP_INTERVAL_S 4	//4000ms = 4s
#define DISPLAY_TIMEOUT_S 10 //5sec

#define true 1
#define false 0

typedef struct{
	uint16_t u16interval;
	uint16_t u16duration;
	uint16_t countdown;
}config_t;

typedef enum{
	DIGIT_INTERVAL,
	DIGIT_DURATION,
	DIGIT_COUNTDOWN,
#ifdef FEATURE_PUMP_STRENGTH
	DIGIT_PUMP_STRENGTH,
#endif
}digit_t;

#define UNUSED(x) (void)(x)

/* Macros to access bytes within words and words within longs */
#define LOW_BYTE(x)     ((uint8_t)((x)&0xFF))
#define HIGH_BYTE(x)    ((uint8_t)(((x)>>8)&0xFF))
#define LOW_WORD(x)     ((uint16_t)((x)&0xFFFF))
#define HIGH_WORD(x)    ((uint16_t)(((x)>>16)&0xFFFF))

#endif /* PLATFORM_H_ */

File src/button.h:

/*
 * BUTTON.h
 *
 *  Created on: 04.01.2019
 *      Author: pmale
 */

#ifndef BUTTON_H_
#define BUTTON_H_

#define BUT_MINUS_INT PCINT18
#define BUT_PLUS_INT PCINT17
#define BUT_SET_INT PCINT19
#define BUT_MAN_INT PCINT20

#define BUTTON_DDR DDRD
#define BUTTON_PIN PIND

typedef enum{
	BUTTON_NO_PRESS=0,
	BUTTON_SHORT_PRESS=2,	//100ms
	BUTTON_LONG_PRESS=16,	//800ms
	BUTTON_LONG_PRESSING,
	BUTTON_PRESSING
}button_press;

typedef enum{
	BUTTON_MINUS = PD3,
	BUTTON_SET = PD2,
	BUTTON_PLUS = PD1,
	BUTTON_MAN = PD4,
	NUM_BUTTONS
}button_t;

typedef struct{
	uint8_t pressed;
	uint8_t duration;
}button_struct;

void button_init();
void button_setPCCallback(void (*func)(void));
button_press button_isPressed(button_t but);
uint8_t button_anyPressed();
void button_clear();
void button_SyncTask(); //50ms




#endif /* BUTTON_H_ */

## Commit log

2019-03-31 uploading current state
2019-03-31 gitignore
2019-03-31 last version built for t841
2019-03-31 add release compile
2019-03-31 adapted pin names
2019-04-01 port of Pin definitions done, compiles without warnings
2019-04-01 no remap necessary
2019-04-01 marking possible bug positions
2019-04-04 bug fixed, removed markings
2019-04-04 New Release
2019-04-04 removing software based I2C Master
2019-04-04 using Atmels own twi master library for t88
2019-04-04 compiles, needs test code now
2019-04-05 first test code
2019-04-05 cleanup done, saved a few kb
2019-04-10 correct button definition, + and - swapped working buzzer, but needs a diode to not destroy the pcb
2019-04-10 adding current and setup temp to DATA adding duration adjustment implementation
2019-04-22 enable PWR_IN
2019-04-22 update Build number this release is on the first 4 pcbs sent to HQ
2019-04-22 update binary
2019-04-22 set countdown value to normal hours
2019-04-29 adding boot animation fixing PowerInput switch from Powerbank to battery, reset pin was the issue
2019-05-18 display reset flag for debugging
2019-05-18 buzzer tested
2019-05-19 using peter fleury i2c library
2019-05-19 remove test code
2019-06-26 moved files removed temp sensor from code, as it causes system brick
2019-06-26 update...
2019-06-26 getting Release ready
2019-06-26 fixing parasitic power of 7segment ic over data line
2019-06-26 adding: disconnect PB while active -> go to sleep
2019-06-26 implemented powerState such that it runs independently removed powerChange callback
2019-06-26 implemented buzzer using circular buffer. This way the tones will now be played without blocking not completely bugfree yet. Plays an annoying 4s tone sometimes
2019-06-27 adding pump test and sig pin checking if power lost while pumping and goto sleep tweaking buzzer
2019-06-28 using Frequency Lookup Table instead of division inside interrupt routine to mitigate performance issues Adding a pump disable once power is lost while pumping
2019-06-28 changing ADC from onDemand to Free Running mode Implemented a ringBuffer to remove ADC measurement spikes
2019-06-28 adding a ADC Stable flag which signalizes if 10 measurements are completed after initialization
2019-08-17 disable heartbeat fix adc_stable
2019-08-18 working on v1.3
2019-08-18 implementing capLow Recharge implementing PB Empty Alarm
2019-08-20 removed buzzer display timeout to 5s load counter to 2s
2019-09-07 adding a wakeUpState
2019-09-07 Use Buzzer pin as sleep debug pin. LOW if in sleep, HIGH if active
2019-09-08 fixing
2019-11-15 add charge cap functionality removed pump power lost feature
2020-01-31 ported ide to vscode platformio removed Release.zip, using Bitbucket Releases from now on
2020-02-28 first step
2020-03-01 finished basic port, compiles.
2020-03-01 optimizing state machine, adding comments
2020-03-08 cleanup of power
2020-03-14 buttons working, power detection still patched out
2020-03-16 fixed hello animation fixed pump counter using 5V Pin for isPowerConnected -> works great! after reset -> blink blue if no PB connected -> blink green if PB connected
2020-03-21 Adding MAN Long Press in Config mode for resetting data. Using 5V Pin for Power detection
2020-03-22 hub implementation
2020-04-07 some updates
2020-04-11 pull down i2c and tm pins in sleep to keep 5V low use ADC for cap measurement instead of BOD -> disable by fuses again
2020-04-12 implementing Clock Output for voltage doubler
2020-04-12 switched back to 1MHz
2020-04-23 fixing LED blink
2020-04-30 testing of new LoadCircuit
2020-05-09 tweaking timings
2020-05-09 Adding Info Screen, Moving Reset to Info Screen
2020-05-09 fixing BlinkDelay
2020-05-10 reimplemented temp
2020-05-10 Fixed Temp Display Fixed Blinking Added totalRuntime, saves every day Fixed HubDisplay Removed Pump Decrement below 1min
2020-05-11 renamed Signal moved all Pin Definitions to PLATFORM.h
2020-05-14 Disable Brownout Remove Display Charge Animation, replacing with LED Fade replace all delays with Short Sleeps Add Solar Signal 1sec before wakeup of powerbank Increase LowVoltage to 3V Fixing Temp S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
2020-05-14 Release 1.3.4: Optimized energy consumption and UX
2020-05-20 - added status bits and ignore status bits to data structure - added error state to display last error - removed boot animation, directly to sleep on powerup - added separate charge state, with no UI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
    - changed button threshold to 50ms
    - code cleanup
2020-05-20 - added ignoreFunctionality - added customCountdown Function for delayed PBTest - fixed glitchy Display Wake - added PBError Functionality - Pump Test not working on current HW, removed
2020-05-20 new Release v1.4.0
2020-06-22 Changed Sleep Timer Source from WDT to Timer0, 250ms Timer Timer1 now responsible for both Clock Source and active 1ms Clock Included CRC Protection for EEPROM Corruption Detection Implemented EEPROM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
2020-09-09 new default data
2020-09-12 applied changes for new hardware. Removed Pump Check. Added multiple LEDs
2020-09-12 fixed double wakeup bug renamed to SHOW_ERROR moved decCountdown out of ISR
2020-09-12 fixed timer sleep not feeding watchdog disabling solar charger for now
2020-09-14 fixed runtime Timer added savePending to EEPROM to delay save to higher voltage state fixed EEPROM CRC added redgreen LED Blink
2021-08-06 - version 1.4.6, massively improved EEPROM saving
2022-01-17 - lets build a map - initial: 8140Bytes Flash, 179Bytes RAM - now: 8120 Flash by saving an if
2022-07-01 - simplified display code
2022-07-06 - changed pin definitions for hw1.4.4 - added multiple environments to build multiple targets
2022-07-08 - adding strength data
2022-07-08 - removing temp sensor
2022-07-08 - Feature Pump Strength done
2023-02-26 cleanup and add readme
2023-02-27 typos
2024-04-19 - fix platformio config - add pump oscillating feature
2024-04-19 update BRD and BOM
2024-04-19 add kicad files
2024-05-02 - starting with port to atmega328p
2024-05-05 - switched back to 1.8V BOD, necessary for Solar PB - increased blink Delay while sleep to 8s and charging to 4s - added charging dependency on PB Fill State - modified wake pattern - increased Cap c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
2024-05-07 - simplify wakeup code - added 2.5s delay beofre starting to pump - added pump start animation
2024-06-02 enable Blinking on Display Screen
2024-06-08 update PCB to 1-sided for price estimation
2024-06-12 - added 5V Pin debouncing
2024-07-10 add clearing of PB Error, when the last pump cycle was successful
2025-04-19 Kicad update

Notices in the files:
parts and their libraries:
Wurth_Connectors_WR-USB: Copyright: Würth Elektronik
SparkFun-PowerSymbols: Licensing: Creative Commons ShareAlike 4.0 International - https://creativecommons.org/licenses/by-sa/4.0
